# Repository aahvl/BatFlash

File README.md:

# BatFlash

## To simply put it: Lighting up PCB of Batman!
Flashes 10x LED lights nicely, and pairs up with the stand!

3d viewer of the pcb and case!
https://cad.onshape.com/documents/c219ef60a494501278e8c30c/w/ee144ded872afe413f11f483/e/88ae849e3cbbe26816d39422?renderMode=0&uiState=6a3ae0b0769c0c0f5aa7bb4b

### BOM:
10x LED Lights of your choice.
NE555P
CD4017
Connector Pins
Electrolytic capacitor
Resistor
Potentiometer

---

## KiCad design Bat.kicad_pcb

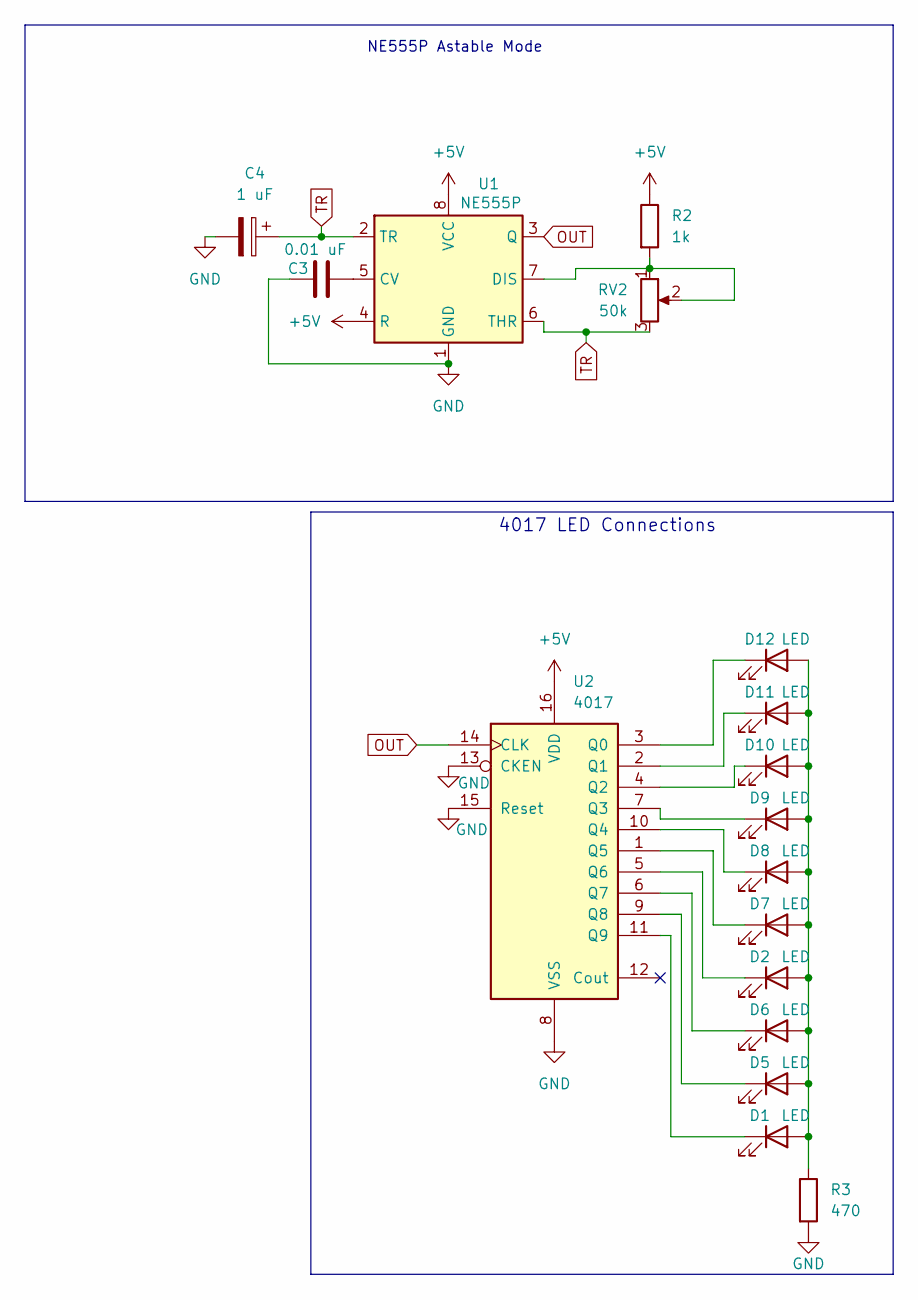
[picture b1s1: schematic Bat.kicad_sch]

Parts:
C3: 0.01 uF; C_Disc_D7.0mm_W2.5mm_P5.00mm
C4: 1 uF; CP_Radial_D5.0mm_P2.00mm
D1, D2, D5, D6, D7, D8, D9, D10, D11, D12: LED; LED_D3.0mm
R2: 1k; R_Axial_DIN0207_L6.3mm_D2.5mm_P7.62mm_Horizontal
R3: 470; R_Axial_DIN0207_L6.3mm_D2.5mm_P7.62mm_Horizontal
RV2: 50k; Potentiometer_Vishay_T93YA_Vertical
U1: NE555P; DIP-8_W7.62mm
U2: 4017; N16

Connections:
+5V: R2.1, U1.4 (R), U1.8 (VCC), U2.16 (VDD)
GND: C3.1, C4.2, R3.2, U1.1 (GND), U2.8 (VSS), U2.13 (CKEN), U2.15 (Reset)
unnamed: D1.2 (A), D2.2 (A), D5.2 (A), D6.2 (A), D7.2 (A), D8.2 (A), D9.2 (A), D10.2 (A), D11.2 (A), D12.2 (A), R3.1
unnamed: D1.1 (K), U2.11 (Q9)
unnamed: D2.1 (K), U2.5 (Q6)
unnamed: D5.1 (K), U2.9 (Q8)
unnamed: D6.1 (K), U2.6 (Q7)
unnamed: D7.1 (K), U2.1 (Q5)
unnamed: D8.1 (K), U2.10 (Q4)
unnamed: D9.1 (K), U2.7 (Q3)
unnamed: D10.1 (K), U2.4 (Q2)
unnamed: D11.1 (K), U2.2 (Q1)
unnamed: D12.1 (K), U2.3 (Q0)
unnamed: C3.2, U1.5 (CV)
unnamed: R2.2, RV2.1, RV2.2, U1.7 (DIS)
OUT: U1.3 (Q), U2.14 (CLK)
TR: C4.1, RV2.3, U1.2 (TR), U1.6 (THR)

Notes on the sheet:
4017 LED Connections
NE555P Astable Mode

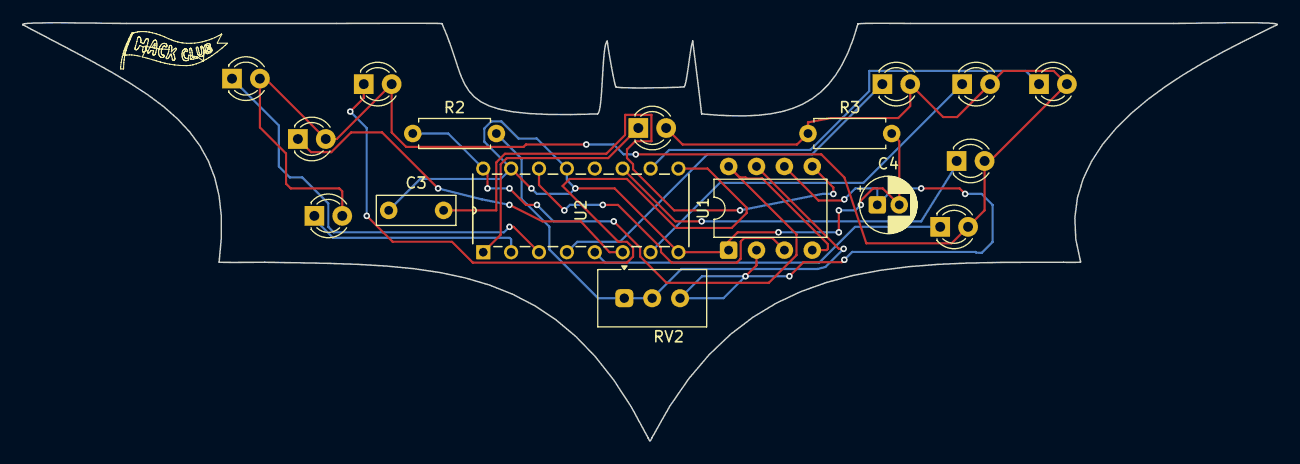
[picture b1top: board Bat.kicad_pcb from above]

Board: 2 copper layers, 114.3 x 38.1 mm, 17 parts (0 on the bottom side), 17 nets.

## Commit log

2026-05-05 Update README with PCB details and note
    Added note about corrupted 3D model of the PCB.
2026-06-03 Update README with image and maintain content
    Added an image to the README and preserved the existing content.
2026-06-03 Update README.md with additional image x2
    Added an additional image to the README and preserved existing content.
2026-06-03 Revise README for clarity and project description
2026-06-03 3D Printable Stand
2026-06-03 Enhance README with LED functionality and BOM details
    Added description of LED flashing functionality and updated BOM.
2026-06-23 Add journal entry about BATMAN dxf files
2026-06-23 Update README with additional PCB viewer link
